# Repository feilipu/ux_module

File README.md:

# User Experience Module

User Experience Module is designed to use with the RC2014.

It provides a VGA output, and PS/2 keyboard input. It also provides a FTDI Basic serial connector, which normally operates in parallel to the VGA/keyboard.

It is designed to operate as an MC68B50 ACIA device (the standard RC2014 Serial Module), so that it can be used without modifying the standard ROMs in circulation.

## Pictures

<div>
<table style="border: 2px solid #cccccc;">
<tbody>
<tr>
<td style="border: 1px solid #cccccc; padding: 6px;"></td>
</tr>
<tr>
<th style="border: 1px solid #cccccc; padding: 6px;"><center>User Experience Module for RC2014 - Production</center></th>
</tr>
</tbody>
<tbody>
<tbody>
<tr>
<td style="border: 1px solid #cccccc; padding: 6px;"></td>
</tr>
<tr>
<th style="border: 1px solid #cccccc; padding: 6px;"><center>User Experience Module for RC2014 - Pre-Production</center></th>
</tr>
</tbody>
<tbody>
<tr>
<td style="border: 1px solid #cccccc; padding: 6px;"></td>
</tr>
<tr>
<th style="border: 1px solid #cccccc; padding: 6px;"><center>User Experience Module for RC2014 - Production Schematic</center></th>
</tr>
</tbody>
</tbody>
<tbody>
<tr>
<td style="border: 1px solid #cccccc; padding: 6px;"></td>
</tr>
<tr>
<th style="border: 1px solid #cccccc; padding: 6px;"><center>User Experience Module for RC2014 - Production Board Layout</center></th>
</tr>
</tbody>
</table>
</div>

## Supported System ROMs

### RC2014 Standard

The UX Module emulates an ACIA interface on base port `0x80`, as per the standard RC2014 usage. Ports `0x80` and `0x81` are required for the implementation.

This supports the use of [standard RC2014 ROMs](https://github.com/RC2014Z80/RC2014/blob/master/ROMs/Factory/README.md) for MS Basic and CP/M as distributed. These ROMs include:

 - R - Microsoft BASIC, for 32k RAM, 68B50 ACIA, with origin 0x0000
 - K - Microsoft BASIC, for 56k RAM, 68B50 ACIA, with origin 0x0000
 - 1 - CP/M Monitor, for pageable ROM, 64k RAM, 68B50 ACIA, CF Module at 0x10, with origin at 0x0000
 - 88 - Small Computer Monitor for pageable ROM, 64k RAM, SIO/2 or 68B50 ACIA, with Microsoft BASIC and CP/M boot options
 - 9 - Small Computer Monitor for any ROM, any RAM, any UART

### CP/M-IDE

The [CP/M-IDE for ACIA](https://github.com/RC2014Z80/RC2014/tree/master/ROMs/CPM-IDE) can be used where an [IDE Interface Module](https://www.tindie.com/products/semachthemonkey/rc2014-ide-hard-drive-module/) is available.

### RomWBW

[RomWBW](https://github.com/wwarthen/RomWBW) is supported, and the UX Module appears as an ACIA port. The UX Module was not compatible with the ACIA device detection mechanism in the 3.0.1 Release, due to the UX Module's tight addressing. However, the device detection mechanism has been improved in the 3.1.1 development branch and it works with the UX Module.

An optimal configuration of RomWBW is to have the UX Module mapped to `0x40`, and a SIO Module providing `TTY` ports. The minimal boot message for this looks like this...

```sh

RomWBW HBIOS v3.1.1-pre.43, 2021-02-11

RC2014 Z80 @ 7.372MHz
0 MEM W/S, 1 I/O W/S, INT MODE 1, Z2 MMU
512KB ROM, 512KB RAM

SIO0: IO=0x80 SIO MODE=115200,8,N,1
SIO1: IO=0x82 SIO MODE=115200,8,N,1
ACIA0: IO=0x40 ACIA MODE=115200,8,N,1
MD: UNITS=2 ROMDISK=384KB RAMDISK=256KB
PPIDE: IO=0x20 PPI NOT PRESENT

Unit        Device      Type              Capacity/Mode
----------  ----------  ----------------  --------------------
Char 0      SIO0:       RS-232            115200,8,N,1
Char 1      SIO1:       RS-232            115200,8,N,1
Char 2      ACIA0:      RS-232            115200,8,N,1
Disk 0      MD1:        RAM Disk          256KB,LBA
Disk 1      MD0:        ROM Disk          384KB,LBA

RC2014 Boot Loader

Boot [H=Help]:
```

RomWBW finds the SIO channels before the ACIA. One SIO/2 chip uses character units 0 and 1. The UX Module (ACIA) is then unit 2. Set `BOOTCON` to 2 so the console is the ACIA. The key lines of the configuration file are below.

```sh
UARTENABLE  .SET    FALSE       ; UART: DISABLE 8250/16550-LIKE SERIAL DRIVER (UART.ASM)
;
ACIAENABLE  .SET    TRUE        ; ACIA: ENABLE MOTOROLA 6850 ACIA DRIVER (ACIA.ASM)
ACIA0BASE   .SET    $40         ; ACIA 0: REGISTERS BASE ADDR TO AVOID SIO/2 BASE ADDRESS
;
SIOENABLE   .SET    TRUE        ; SIO: ENABLE ZILOG SIO SERIAL DRIVER (SIO.ASM)
SIOCNT      .SET    1           ; SIO: NUMBER OF CHIPS TO DETECT (1-2), 2 CHANNELS PER CHIP
;
TMSENABLE   .SET    FALSE       ; TMS: DISABLE TMS9918 VIDEO/KBD DRIVER (TMS.ASM)
;
BOOTCON     .SET    2           ; SET ACIA AS CONSOLE, ASSUMING 1 SIO/2 MODULE CONFIGURED WITH 2 CHANNELS
```

## Construction

Building the UX Module is fairly straightforward. Some notes are included below describing options and potential issues that may arise.

### BOM

The BOM for the UX Module can be found in the Production PCB section of this repository, both listing [by parts](https://github.com/feilipu/ux_module/blob/main/pcb/RC2014_UX_MODULE_ListByParts.csv), and listing [by values](https://github.com/feilipu/ux_module/blob/main/pcb/RC2014_UX_MODULE_ListByValues.csv).

Also, a complete ordering [Cart is available at Digikey AU](https://www.digikey.com.au/short/47vbdp).

Note that the 74HC4078 NOR device is not included in the Digikey BOM. This device is obsolete, but can be obtained from UT Source or other ebay sources (or as an option on Tindie).

Note that sockets are not included in the BOM, but can be used if desired. See the notes on Overclocking below.

### SMD

Soldering the SMD devices is fairly straightforward. The resistors go on the front of the board. They are not polarised, but if you are concerned with neatness they can all be aligned so they face the same way. The capacitors go on the back of the board. The three 200 pF capacitors (C12, C13, C16) are mounted behind the diodes. A through-hole on either side of the pads marks that location.

There are many techniques for soldering SMD. For a simple tutorial using a standard fine tipped soldering iron and a pair of tweezers, [please refer to this video](https://youtu.be/t7WQLCaeAjM).

### EEPROM I2C

The Parallax Propeller MCU stores its firmware in an external I2C EEPROM. The minimum requirement is for 256kb size (32kB), but the bootloader also supports 512kb size (64kB) devices. Either device is suitable for the UX Module. If you are interested to do additional coding it might be sensible to equip the 512kb device.

There is no need to put the EEPROM in a socket, as it can be programmed in-situ about a million times (literally) and you're never going to need to exchange it.

The bootloader uses P28 as SCL and P29 as SDA. VGA DDC on this board is swapped (P29 SCL, P28 SDA). That match is VGA pin 15 and pin 12. A monitor EDID chip then does not ACK during boot. After boot, `i2c.startCog` in `ddc_i2c.spin` uses that swapped pair to read the display. Do not use that cog to talk to the 24LC256.

### Overclocking

The Parallax Propeller is specified to run at 80MHz. The typical mechanism to achieve this is to provide a 5MHz crystal or oscillator and use the Propeller internal 16x PLL capability to generate the 80MHz system clock.

Of course this specification can be stretched and the maximum system clock seems to be about 120MHz, noting that this is right on the edge of the capabilities.

The UX Module is expecting a 7.3728MHz oscillator, the same standard clock as the RC2014 Z80, which produces a 118MHz Propeller system clock.

It is possible to use a slower oscillator at 5MHz, or 6.25MHz, or other if desired, or in the unlikely event your selected Propeller device doesn't work at 118MHz. In this case the clock rate specification [`_xinfreq`](https://github.com/feilipu/ux_module/blob/main/src/ux_module.spin#L12) will have to be adjusted in the firmware to suit, and the VGA video timing will need to be adjusted to suit. If you are concerned about this it would be sensible to mount the oscillator in a socket to enable it to be simply swapped as needed.

## Firmware Development

The UX Module firmware is developed in Propeller SPIN, and in Propeller Assembly (PASM). The individual functions are mainly built in PASM, with connecting higher level logic running in SPIN.

### Development Environment (humans)

There are a number of alternative programming environments for the Parallax Propeller. The PropellerIDE was defined as the default option, and was developed to be cross-platform capable. However, other solutions supporting SPIN, PASM, and C or C++ are also available.

Use PropellerIDE for interactive edits. The command-line path below is for scripts and agents.

The [PropellerIDE](https://developer.parallax.com/propelleride/) is available for Windows, OS X, Linux, and packaged for debian.

### Command-line build (humans, agents, and scripts)

Use the CLI toolchain. PropellerIDE remains valid for interactive work. Both paths target **Propeller 1 (P8X32A)** only. Do not use Propeller 2 loaders (`loadp2`) or PASM2.

| Tool | Role | Source |
|------|------|--------|
| [OpenSpin](https://github.com/parallaxinc/OpenSpin) (`openspin`) | Compile Spin and PASM to a `.binary` or `.eeprom` image | Build from source (for example `~/Projects/OpenSpin`) |
| [PropLoader](https://github.com/parallaxinc/PropLoader) (`proploader`) | Load the image over FTDI FT232 (DTR reset) | Build from source (for example `~/Projects/PropLoader`) |
| `tools/ux-load.sh` | EEPROM load + run on `/dev/cu.usbserial-*` | This repository |
| `tools/ux-screen.sh` | 115200 8N2 FTDI console. Holds DTR off | This repository |
| `rc-screen` (`tools/rc-screen.sh`) | 115200 8N2 ACIA console on USB CDC or FTDI. Direct GNU `screen` | `$HOME/bin` |

Copy this block. Quit GNU `screen` first (`C-a k`). The serial port must be free.

```sh
mkdir -p build
openspin -u -L src -L src/lib_vjet -b -o build/ux_module.binary src/ux_module.spin
tools/ux-load.sh
tools/ux-screen.sh
```

Top object is `src/ux_module.spin`. The product compile needs `-u`, `-L src`, and `-L src/lib_vjet`. A VECTORJET demo top is in `src/lib_vjet/demo/` and uses the same search path.

`tools/ux-load.sh` writes EEPROM then runs. It uses DTR reset (SparkFun FTDI Basic pin 6). It refuses USB CDC (`/dev/cu.usbmodem*`). CDC is console only.

Same load without the helper. Adjust the device from `proploader -P`. Prefer `/dev/cu.*` over `/dev/tty.*` on macOS.

```sh
proploader -p /dev/cu.usbserial-XXXX -e -r build/ux_module.binary
```

Full helper notes, VECTORJET compile, and screen keys: [`tools/README.md`](tools/README.md). Agent rules: `AGENTS.md`, `.agents/skills/tool-propeller/`, and `.agents/skills/tool-rc-screen/`.

### Programming Interface

The UX Module provides a standard FTDI Serial interface for programming. This can optimally be at 3V3, but also works at 5V. References to "Prop Plug" in the PropellerIDE should be taken to mean the FTDI Serial device that you're using. The same FTDI FT232 path is what `proploader` uses from the command line.

When programming the UX Module firmware with PropellerIDE, it is important that the [upper level code](https://github.com/feilipu/ux_module/blob/main/src/ux_module.spin) be the active window when clicking "compile and upload". The PropellerIDE will compile and upload a sub-module file if it thinks this is what you wanted (because you left it in the foreground). Of course this will lead to things not working as expected. You'll just need to do it again with the upper most code in the foreground.

### Source Code Hierarchy

Propeller SPIN works with modules which help to mask details from driver code from upper level code.

To implement the functions required for the UX Module several SPIN/PASM modules previously written for Propeller by Parallax have been used. This means that the pretested modules from the Parallax "Object Exchange" are used, and that we can focus on how these modules are integrated.

The ACIA bus cog is PASM written for this board. It is in the [ACIA module](https://github.com/feilipu/ux_module/blob/main/src/acia_rc2014.spin). VECTORJET adds the slice VGA cog and the render cogs under `src/lib_vjet`. The text VGA cog is the Parallax hires text driver.

`ddc_i2c.spin` also runs a Spin cog after boot. It talks to the monitor on the VGA DDC pins (swapped vs the boot EEPROM). It reads EDID at `0x50` and, if the display answers, DDC/CI at `0x37`. It does not change VGA timing.

VECTORJET (`src/lib_vjet`) is linked from the product top. Boot is the text console. A good sealed list starts graphics. The beam-chase demo is `src/lib_vjet/demo/vjet_test.spin`. The live picture is the eight-line scan. Failed tear repairs are in `3D_PROCESS_LIB_VJET.md`. The framebuffer sources were removed. Git history keeps them.

The library objects stay in `src/lib_vjet/`. Compile tops and the beam-chase head are in `src/lib_vjet/demo/`. Display lists are in `src/lib_vjet/scene/`. A top defines one scene and includes the head. The head includes that scene file. It does not include `scene_cube.spin`. Compile with `-L src -L src/lib_vjet`.

```
src/lib_vjet
|
|---> VJET_v01_displaylist
|---> VJET_vUXM_rendering
|---> VJET_vUXM_vga
|---> hexfont
|---> demo/
|     |---> head_slice          included by a top. Not a compile top.
|     |---> vjet_test           triangles
|     |---> vjet_card           test card
|     |---> vjet_stress         stress picture
|     |---> vjet_probe          orbit probe
|     |---> graphtest           graph sample
|     |---> vjet_acia           ACIA check
|     |---> vjet_ftdi           FTDI check
|     |---> vjet_spin           extra Spin cog check
|---> scene/
      |---> scene_triangles
      |---> scene_graph
      |---> scene_probe
      |---> scene_card
      |---> scene_stress
      |---> scene_cube          mesh only. The head does not include it.
```

```
ux_module.spin
|
|---> terminal_ftdi
|---> keyboard_ps2
|---> acia_rc2014
|---> ddc_i2c                 text mode only
|---> wmf_terminal_vga        the screen is the first 3200 bytes of list A
|     |
|     |---> hires_text_vga
|---> VJET_vUXM_vga           graphics mode
|---> VJET_vUXM_rendering
|---> VJET_v01_displaylist
|---> hexfont
|---> scene/scene_card        included picture
```

Three programs make one moving picture. The author writes one sealed list. The host transfers that list on the ACIA console. The Propeller presents it on the front porch. The names and the game loop are under Frames in `ARCHITECTURE_LIB_VJET.md`.

## Usage Notes

When the UX Module has been programmed successfully, it should boot with `UX Module Initialised` appearing on both VGA interface (screen) and on the FTDI Serial interface.

To reboot the UX Module the `DTR` on the FTDI interface needs to be toggled. This can be done with the PropellerIDE, or with any serial terminal that can trigger `DTR` toggle. This functionality is used by the Arduino family, so the function is quite common within serial terminals.

To reboot the UX module if operating stand-alone, the DTR (`GRN`) pin can be touched to the ground (`BLK`) pin on the serial interface, or alternatively touched to the grounded case of the PS/2 keyboard connector.

Once the UX Module is running the ACIA emulation is enabled, so the RC2014 Z80 can now be rebooted. This can be done by pressing the RESET button on the RC2014 or, if a PS/2 keyboard is attached, by pressing `CTRL+ALT+DEL`. This will now initiate a normal RC2014 boot sequence.

This video below shows the expected output of a session.

<BR>
CLICK IMAGE TO VIEW!

This video shows the lib_vjet pictures on the UX Module.

<BR>
CLICK IMAGE TO VIEW!

### Ports

The UX Module emulates an ACIA interface on base port `0x80`, as per the standard RC2014 usage. Ports `0x80` and `0x81` are required for the implementation.

The UX Module can be alternately located on ports `0x40`, `0x41` or on `0xC0`, `0xC1`.

The sealed-list path uses the ACIA console. The mark is `$1C`. `$07` switches graphics. Ports `0xC0` and `0xC1` stay reserved. `PORT_VJET` in `ux_module.spin` is that base. Boot remains the ACIA text console.

### Video VGA

If you do not have a VGA monitor, it is possible to attach a VGA->HDMI adaptor. The VGA connector on the UX Module supplies 5V to the adaptor so no additional power connection (via USB) is required. The recommended VGA->HDMI adaptor is from [Vention and is available here](https://www.aliexpress.com/item/32844619223.html).

The VGA timings (front porch and back porch) have been developed using the Vention HDMI adaptor. If an alternative HDMI adaptor or actual VGA monitor is used, the timings may need to be adjusted to ensure that all characters are visible.

The active text table in `hires_text_vga.spin` is 640×480 at about 70 Hz (80×40 characters). Other Chip Gracey tables (1024×768, 800×600, 640×480 at 85 Hz) are in the same file, commented out. Timing is compile-time. EDID reports the preferred mode. DDC/CI cannot set resolution or aspect. Many HDMI adaptors answer EDID and do not answer DDC/CI (`0x37`).

### Keyboard PS/2

The keyboard is presumed to be a [USA standard](https://github.com/feilipu/ux_module/blob/main/src/keyboard_ps2.spin) keyboard. Alternate key maps are possible, and can be added to your own build of the firmware.

### RC2014 Bus Tx/Rx Line Conflict

When multiple serial Modules are used on one RC2014 Backplane, there is a potential for conflict on the Tx/Rx lines, Pin 35 and 36. A conflict on bus pins 35 (TX) and 36 (RX) stops the RC2014 boot.

The UX Module is connected to the RC2014 Bus serial Tx and Rx lines. When using the UX Module with other serial Modules (such as the SIO/2 Module), it is necessary to disconnect one or other of the serial Modules. In practice the easiest way to do this is to straighten either the UX Module or SIO/2 Module Tx and Rx pins sufficiently so that they do not insert into the Bus connector.

## Errata Propeller /RESET Pin

The Propeller MCU `/RESET` pin is driven by the serial interface `DTR` pin, which is normally held high when the port is ready. Linux, macOS, and Windows sometimes toggle `DTR` when they open a serial port. This impacts our ability to use the serial interface to upload code to the RC2014.

There are several options proposed on the internet to avoid this issue (mainly driven by Arduino users wanting to have "long running" code). The solutions are written into [`tools/serial_tool.py`](tools/serial_tool.py), which is included to simplify uploading BASIC programs to the RC2014.

For some machines, none of the software options work so the final solution is to bend the `DTR` pin out from the FTDI connector. Then an optional connection can be provided to enable Propeller reprogramming. Photos demonstrating one method to do this are provided in the [`docs`](https://github.com/feilipu/ux_module/tree/main/docs) directory.

## Code of conduct

See the [Code of Conduct](https://github.com/feilipu/ux_module/blob/main/CODE_OF_CONDUCT.md).

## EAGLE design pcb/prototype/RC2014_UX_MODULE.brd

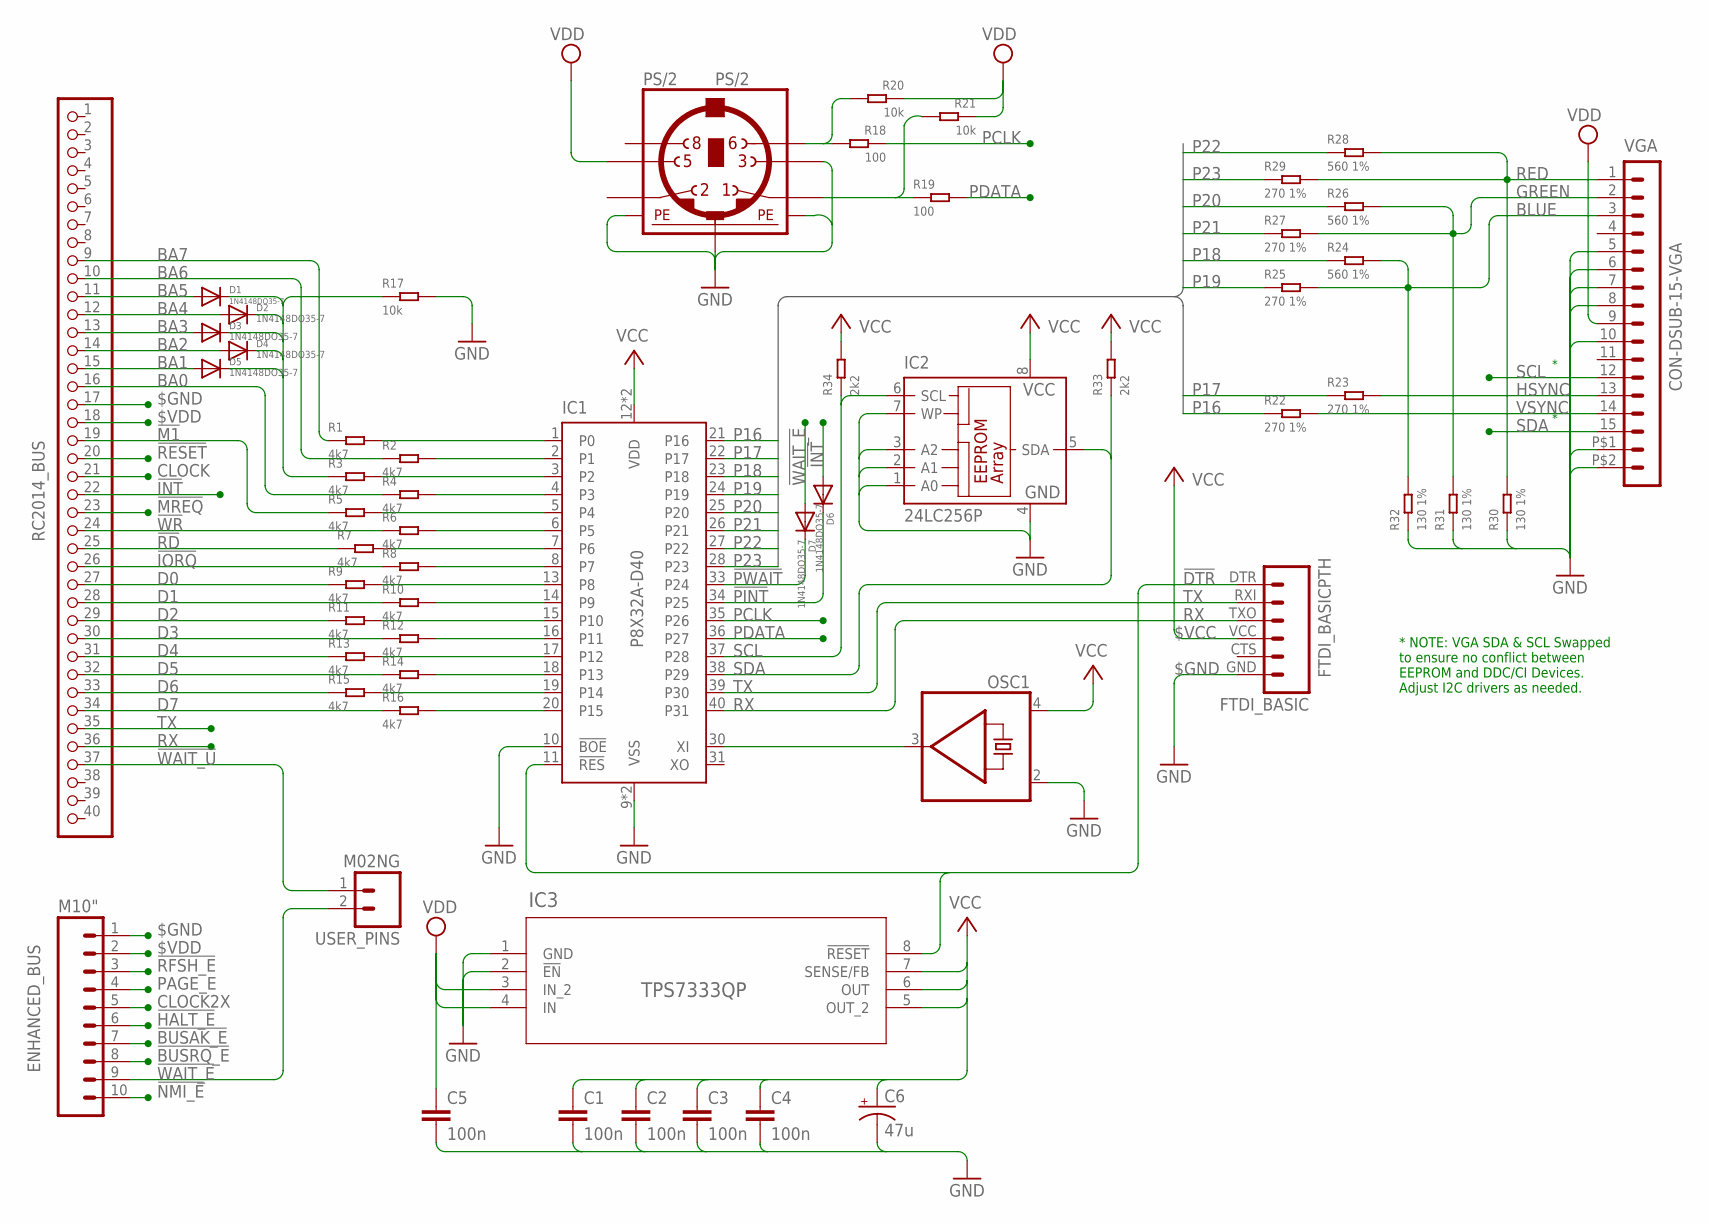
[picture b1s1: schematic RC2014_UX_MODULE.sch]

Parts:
C1, C2, C3, C4, C5: 100n; C025-025X050
C6: 47u; CPOL-RADIAL-100UF-25V
D1, D2, D3, D4, D5, D6, D7: 1N4148DO35-7; DO35-7
ENHANCED_BUS: M10"; 1X10
FTDI_BASIC: FTDI_BASICPTH; FTDI_BASIC
IC1: P8X32A-D40; DIL40
IC2: 24LC256P; DIL8
IC3: TPS7333QP; P8_TEX
OSC1: SG531; DIL08-4
PS/2: PS/2; M_DIN6
R1, R2, R3, R4, R5, R6, R7, R8, R9, R10, R11, R12, R13, R14, R15, R16: 4k7; R0207_7
R17, R20, R21: 10k; R0207_7
R18, R19: 100; R0207_7
R22, R23, R25, R27, R29: 270 1%; R0207_7
R24, R26, R28: 560 1%; R0207_7
R30, R31, R32: 130 1%; R0207_7
R33, R34: 2k2; R0207_7
RC2014_BUS: RC2014 BUS; 1X40
USER_PINS: M02NG; 1X02
VGA: CON-DSUB-15-VGA; 181-015-212-171

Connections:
!BUSAK_E: ENHANCED_BUS.7
!BUSRQ_E: ENHANCED_BUS.8
!DTR: FTDI_BASIC.DTR (1), IC1.11 (!RES), IC3.8 (!RESET)
!HALT_E: ENHANCED_BUS.6
!INT: D6.A, RC2014_BUS.22
!IORQ: R8.1, RC2014_BUS.26
!M1: R5.1, RC2014_BUS.19
!MREQ: RC2014_BUS.23
!NMI_E: ENHANCED_BUS.10
!PINT: D6.C, IC1.34 (P25)
!PWAIT: D7.C, IC1.33 (P24)
!RD: R7.1, RC2014_BUS.25
!RESET: RC2014_BUS.20
!RFSH_E: ENHANCED_BUS.3
!WAIT_E: D7.A, ENHANCED_BUS.9, USER_PINS.2
!WAIT_U: RC2014_BUS.37, USER_PINS.1
!WR: R6.1, RC2014_BUS.24
$GND: C1.2, C2.2, C3.2, C4.2, C5.2, C6.2 (-), ENHANCED_BUS.1, FTDI_BASIC.GND (6), IC1.9 (VSS), IC1.10 (!BOE), IC1.29 (VSS), IC2.1 (A0), IC2.2 (A1), IC2.3 (A2), IC2.4 (GND), IC2.7 (WP), IC3.1 (GND), IC3.2 (!EN), OSC1.2 (GND), PS/2.3, PS/2.SH1 (PE1), PS/2.SH2 (PE2), PS/2.SH3 (PE3), R17.2, R30.1, R31.1, R32.1, RC2014_BUS.17, VGA.5, VGA.6, VGA.7, VGA.8, VGA.10, VGA.P$1 (16), VGA.P$2 (17)
$VCC: C1.1, C2.1, C3.1, C4.1, C6.1 (+), FTDI_BASIC.VCC (4), IC1.12 (VDD), IC1.32 (VDD), IC2.8 (VCC), IC3.5 (OUT_2), IC3.6 (OUT), IC3.7 (SENSE/FB), OSC1.4 (VCC), R33.2, R34.2
$VDD: C5.1, ENHANCED_BUS.2, IC3.3 (IN_2), IC3.4 (IN), PS/2.5, R20.1, R21.1, RC2014_BUS.18, VGA.9
BA0: R4.1, RC2014_BUS.16
BA1: D5.A, RC2014_BUS.15
BA2: D4.A, RC2014_BUS.14
BA3: D3.A, RC2014_BUS.13
BA4: D2.A, RC2014_BUS.12
BA5: D1.A, RC2014_BUS.11
BA6: R2.1, RC2014_BUS.10
BA7: R1.1, RC2014_BUS.9
BLUE: R24.2, R25.2, R32.2, VGA.3
CLOCK: RC2014_BUS.21
CLOCK2X: ENHANCED_BUS.5
D0: R9.1, RC2014_BUS.27
D1: R10.1, RC2014_BUS.28
D2: R11.1, RC2014_BUS.29
D3: R12.1, RC2014_BUS.30
D4: R13.1, RC2014_BUS.31
D5: R14.1, RC2014_BUS.32
D6: R15.1, RC2014_BUS.33
D7: R16.1, RC2014_BUS.34
GREEN: R26.2, R27.2, R31.2, VGA.2
HSYNC: R23.2, VGA.13
KCLK: PS/2.6, R18.2, R20.2
KDATA: PS/2.1, R19.1, R21.2
unnamed: IC1.13 (P8), R9.2
unnamed: IC1.14 (P9), R10.2
unnamed: IC1.15 (P10), R11.2
unnamed: IC1.16 (P11), R12.2
unnamed: IC1.17 (P12), R13.2
unnamed: IC1.18 (P13), R14.2
unnamed: IC1.19 (P14), R15.2
unnamed: IC1.20 (P15), R16.2
unnamed: IC1.8 (P7), R8.2
unnamed: IC1.7 (P6), R7.2
unnamed: IC1.6 (P5), R6.2
unnamed: IC1.5 (P4), R5.2
unnamed: IC1.4 (P3), R4.2
unnamed: IC1.3 (P2), R3.2
unnamed: IC1.2 (P1), R2.2
unnamed: IC1.1 (P0), R1.2
unnamed: D1.C, D2.C, D3.C, D4.C, D5.C, R3.1, R17.1
unnamed: IC1.30 (XI), OSC1.3 (OUT)
P16: IC1.21 (P16), R22.1
P17: IC1.22 (P17), R23.1
P18: IC1.23 (P18), R24.1
P19: IC1.24 (P19), R25.1
P20: IC1.25 (P20), R26.1
P21: IC1.26 (P21), R27.1
P22: IC1.27 (P22), R28.1
P23: IC1.28 (P23), R29.1
PAGE_E: ENHANCED_BUS.4
PCLK: IC1.35 (P26), R18.1
PDATA: IC1.36 (P27), R19.2
RED: R28.2, R29.2, R30.2, VGA.1
RX: FTDI_BASIC.TXO (3), IC1.40 (P31), RC2014_BUS.36
SCL: IC1.37 (P28), IC2.6 (SCL), R34.1, VGA.12
SDA: IC1.38 (P29), IC2.5 (SDA), R33.1, VGA.15
TX: FTDI_BASIC.RXI (2), IC1.39 (P30), RC2014_BUS.35
VSYNC: R22.2, VGA.14

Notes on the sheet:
* NOTE: VGA SDA & SCL Swapped to ensure no conflict between EEPROM and DDC/CI Devices. Adjust I2C drivers as needed.

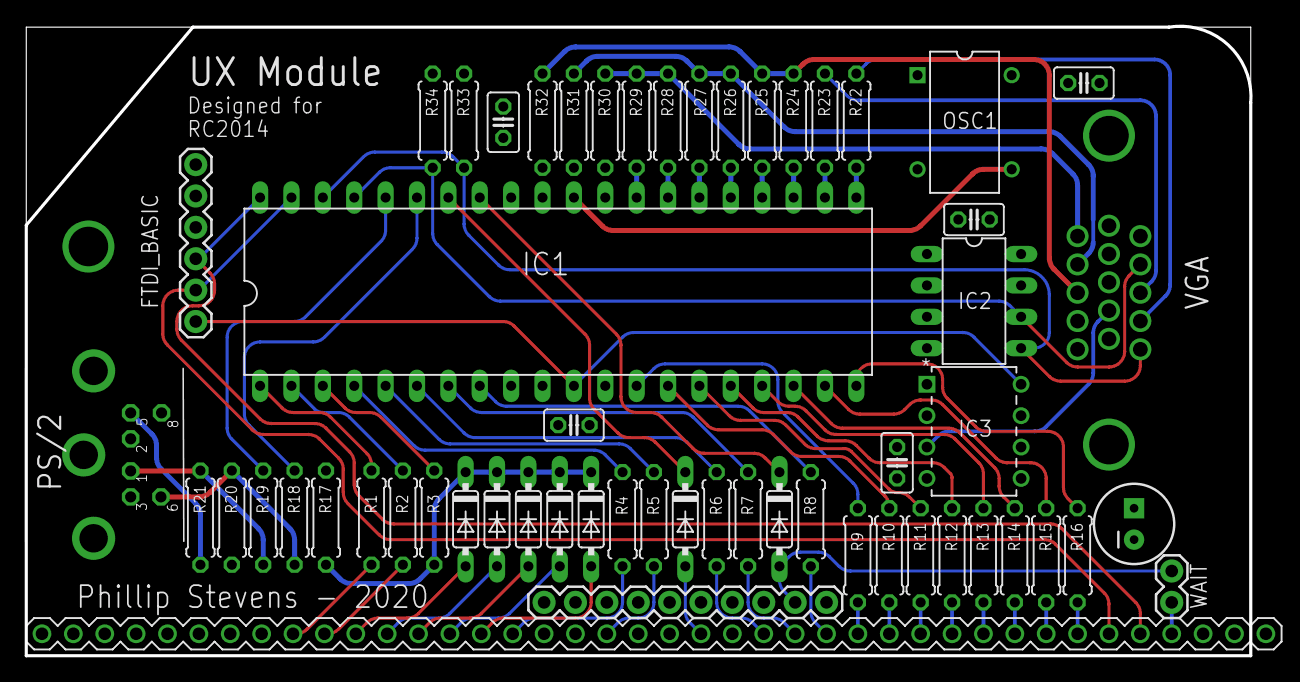
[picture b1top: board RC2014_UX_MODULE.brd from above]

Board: 4 copper layers, 99.1 x 50.9 mm, 57 parts (0 on the bottom side), 68 nets.

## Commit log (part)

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2020-11-22 Propeller OBEX Sourcecode
2020-11-22 rename original code
2020-11-22 Initial ACIA Commit
2020-11-22 revise gitignore
2020-11-22 acia wait improvement
2020-11-25 vga connected
2020-11-26 working state
2020-11-27 FT800 Programmers Guide
2020-12-03 pre-production initial commit
2020-12-04 preproduction update
2020-12-06 some text tweaking
2020-12-10 stability & screen dimensions
2020-12-16 transistor logic adjustments
2020-12-19 rework data delay
2020-12-20 revert to diode logic
2020-12-20 pcb - production
2020-12-23 vga - adjust porch pixels
2020-12-29 ASCII-fy code
    Get rid of Unicode characters in all Spin source files
2020-12-29 Fix compiling in PropTool (and also memory corruption)
2020-12-29 Oh, these two are fine as RES
2020-12-30 directory reorganisation
2020-12-30 add production board graphics
2020-12-30 Update README.md
    copy-pasta.
2020-12-30 organise and complete datasheets
2020-12-30 add docs to pcb zip
2020-12-30 fix file names to reflect content
2021-01-11 ACIA - untangle double buffering
2021-01-11 ACIA - more delay for loaded bus
2021-01-13 README.md - add Tindie link
2021-01-18 add BOM files
2021-01-18 add production jpg
2021-01-18 fix C values in bom
2021-01-25 update README.md with build instructions
2021-01-25 update README.md digikey Cart
2021-01-25 update README.md 74HC4078 note
2021-01-25 add 24LC512 datasheet
2021-02-03 tidy constants and fix ESC
2021-02-03 term input in own cog
2021-02-03 add acia.txFlush
2021-02-08 serial upload tool - options to avoid DTR toggle
2021-02-08 note resolution for DTR managment
2021-02-08 tweaks to screen handling
2021-02-08 add operation video
2021-02-08 add note about rebooting UX Module
2021-02-09 acia - match RomWBW probing
2021-02-09 multi acia wip
2021-02-10 multi-acia updates
2021-02-10 remove copies
2021-02-10 useful fixes from multi_acia
2021-02-10 tidying
2021-02-11 update README.md with RomWBW info
2021-02-11 update README.md with note on Tx/Rx lines
2021-02-11 update README.md with FORCECON RomWBW info
2021-02-17 import VJET library
2021-02-17 import VJET library again
2021-02-17 add VGA 160x120 6-bit example
2021-02-17 add again VGA64
2021-02-17 Use VJET that's not outdated
2021-03-04 Check in customized VJET library, ref #1
    no xasm files RN, those are easy enough to make when there is need
2021-03-05 lib_vjet - schematic & whitespace
2021-03-08 lib_vjet - thought bubbles
2021-03-09 vjet vga - avoid register reuse
2021-03-09 vjet - display list - shape header comments
2021-03-13 implement ANSI VT100 control codes
2021-03-14 clumsy off by 1 fixes
2021-03-14 fresh colours - autumn is out, orchid is in
2021-03-15 no unprintable to screen
2021-03-15 XMODEM Tx filtering
2021-03-16 displaylist whitespace
2021-04-05 update README more
2021-04-16 add DTR toggle (UX Module reset) script
2021-06-01 wip - implement /RTS and XON/XOFF
2021-06-02 wip - flow control
2025-07-23 Fix the values for the 220pF capacitors in the BOM.

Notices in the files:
parts and their libraries:
m-pad-2.1: License : GNU General Public License version 2 (see bottom)
SparkFun: Licensing: CC v3.0 Share-Alike You are welcome to use this library for commercial purposes.
